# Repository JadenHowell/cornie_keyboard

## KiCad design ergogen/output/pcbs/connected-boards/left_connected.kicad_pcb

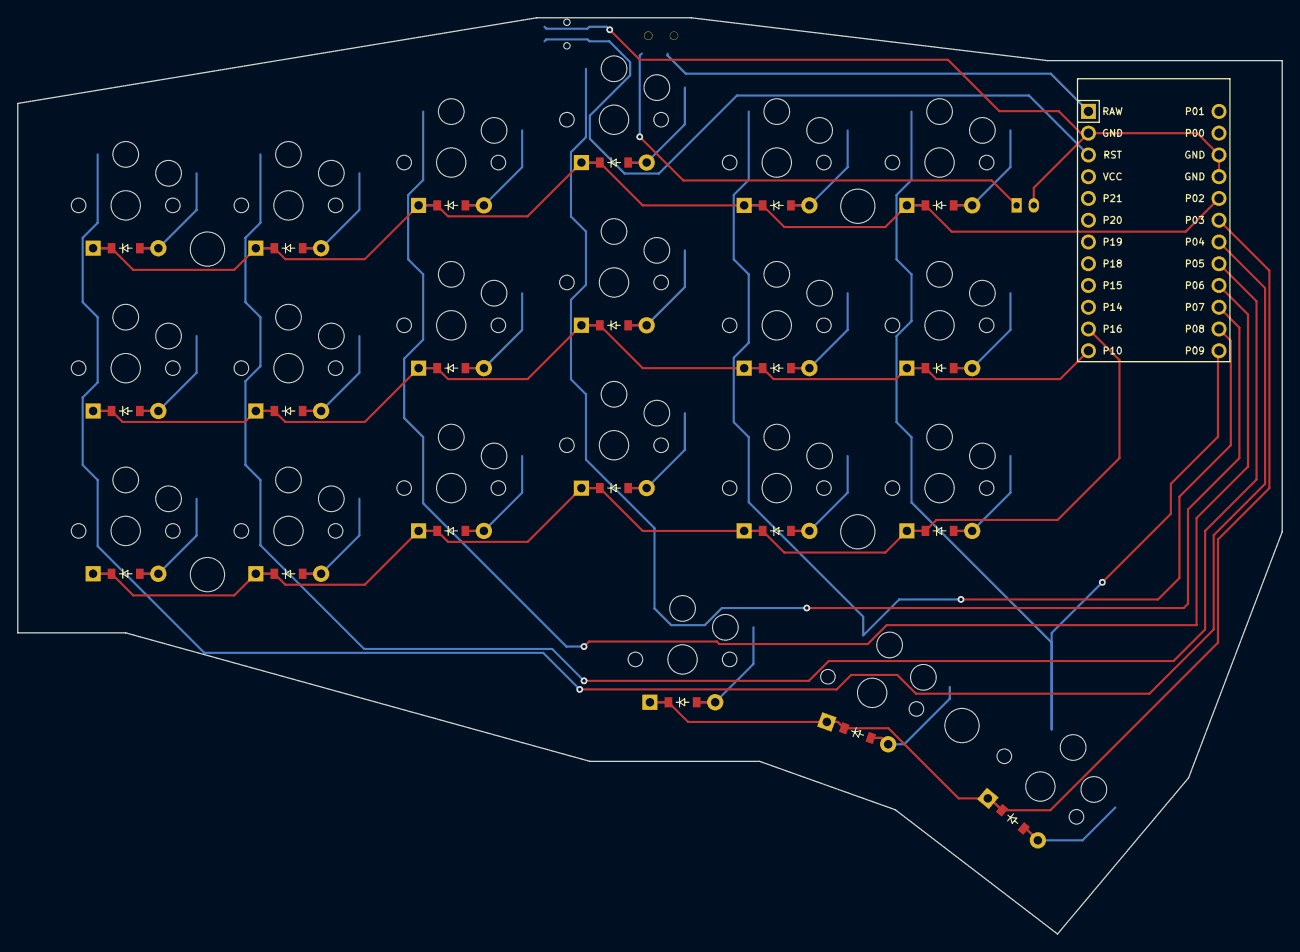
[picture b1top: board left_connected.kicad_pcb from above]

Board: 2 copper layers, 147.6 x 107.0 mm, 46 parts (0 on the bottom side), 35 nets.

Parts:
B1: Panasonic_EVQPUL_EVQPUC
D1, D2, D3, D4, D5, D6, D7, D8, D9, D10, D11, D12, D13, D14, D15, D16, D17, D18, D19, D20, D21: ComboDiode
JST1: JST_PH_S2B-PH-K_02x2.00mm_Angled
MCU1: ProMicro
S1, S2, S3, S4, S5, S6, S7, S8, S9, S10, S11, S12, S13, S14, S15, S16, S17, S18, S19, S20, S21: PG1350
T1: SPDT_C128955

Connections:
GND: B1.1, JST1.2, MCU1.2, MCU1.15, MCU1.16
P2: D3.1, D6.1, D9.1, D12.1, D15.1, D18.1, MCU1.17
P3: D19.1, D20.1, D21.1, MCU1.18
P4: MCU1.19, S1.1, S2.1, S3.1
P5: MCU1.20, S4.1, S5.1, S6.1
P6: MCU1.21, S7.1, S8.1, S9.1
P7: MCU1.22, S10.1, S11.1, S12.1, S19.1
P8: MCU1.23, S13.1, S14.1, S15.1, S20.1
P9: MCU1.24, S16.1, S17.1, S18.1, S21.1
P10: D2.1, D5.1, D8.1, D11.1, D14.1, D17.1, MCU1.12
P16: D1.1, D4.1, D7.1, D10.1, D13.1, D16.1, MCU1.11
RAW: MCU1.1, T1.2
RST: B1.2, MCU1.3
far_thumb: D21.2, S21.2
home_thumb: D20.2, S20.2
index_bottom: D13.2, S13.2
index_home: D14.2, S14.2
index_top: D15.2, S15.2
inner_bottom: D16.2, S16.2
inner_home: D17.2, S17.2
inner_top: D18.2, S18.2
middle_bottom: D10.2, S10.2
middle_home: D11.2, S11.2
middle_top: D12.2, S12.2
near_thumb: D19.2, S19.2
outer_bottom: D1.2, S1.2
outer_home: D2.2, S2.2
outer_top: D3.2, S3.2
pinky_bottom: D4.2, S4.2
pinky_home: D5.2, S5.2
pinky_top: D6.2, S6.2
pos: JST1.1, T1.1
ring_bottom: D7.2, S7.2
ring_home: D8.2, S8.2
ring_top: D9.2, S9.2

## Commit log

2025-09-27 create initial case bottom
2025-09-28 connect pcb lines
